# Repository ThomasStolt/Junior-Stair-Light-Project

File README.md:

# Junior-Stair-Light-Project

This is a smaller/easier/cheaper version of my NeoPixel Stair Light Project. The basic idea is to use a bunch of cheap 12V LEDs stripes attached to your indoor stairs, two IR sensors and an Arduino Nano and animate those LED stripes if a person is walking up or down the stairs.

I created this for a friend of mine. He went out on the internet and bought sets of LED stripes (originally thought for cars, 12V) and mounted them under the stairs. I then went ahead and created this little project around it, giving it some more fun.

For several reasons, all grounds of the LED stripes were connected together and all the positive leads were routed to the circuit for switching/PWM. Because of that, I had to use that dual-transistor circuit, which I found on the internet, to be able to switch the positive lines.
It is actually easier to switch the negative lines, that just requires one transistor/MOSFET, so if you do this and you have a choice, you should probably go with that approach.

Nothing more to add really, just read the circuit under schematics/kicad (there is a PDF) and you should be good.

# Needed Materials:

- Power supply, 12V DC, 2A should be enough (I found a 3A in my mess)
- 1 x Arduino Nano
- 2 x 10k resistors (optional, pull up for PIR sensors, I did not need to use them)
- 1 x 5V regulator (L4940V5)
- 2 x 100uF electrolytic capacitor
- 1 x 100nF ceramic capacitor
- a project box to house the electronics

Then _per step_ you need:
- 1 x LED stripe (12V, for cars)
- 2 x 1kOhm resistor
- 1 x 10kOhm resistor
- 1 x BC337 (or similar) NPN Transistor
- 1 x BC327 (or similar) PNP Transistor

Additionally you need a prototype board (or the PCB, see below) for soldering components, some wires for connecting the components, tools (soldering iron, solder, cutter, clippers, a Dremel helps to cut the copper on the board) and some time and patience.

# Printed Circuit Board
I have created a first "Release Candidate" (RC) of a printed circuit board for this project. I added the maximum number of channels (steps) that an Arduino Nano can have, which is number of Digital outputs + number of Analog outputs - 2 analog outputs (for the IR sensors), which should end up at 18.

So, 18 is the maximum number of steps your stairs can have using this single Arduino Nano module. If you have less stairs, just populate the board with the appropriate number of parts for the channels. If you have more stairs - well, you are on your own.

To order the PCB you'll need to send/upload the Gerber files to a PCB manufacturer of your choice. You can find the Gerber files here: [Gerbes](schematics/kicad/GERBERS), just use the ZIP archive. The board is 9cm x 9cm, currently you get special offers for 2$ for 10 pieces - ridicolous!

As of today (Sep 2018), I have not yet ordered a PCB, so I cannot say whether this PCB is really working, it might still be full of bugs! Try at your own risk!

# Steps:
1. buy all the material
2. create the board (see pictures), start with one channel first
3. test that first channel
4. create all the channels
5. stick it to your stairs

# Pictures

This is the finished board, top view.

This is the finished board on a prototype PCB, bottom view.

These are the connectors for the LED strips, power and IR sensors

The test setup for finishing the code.
I did not have enough left over stripes, hence there are some missing here, but that is sufficient.

This can probably be done on one weekend if you are somewhat experienced.

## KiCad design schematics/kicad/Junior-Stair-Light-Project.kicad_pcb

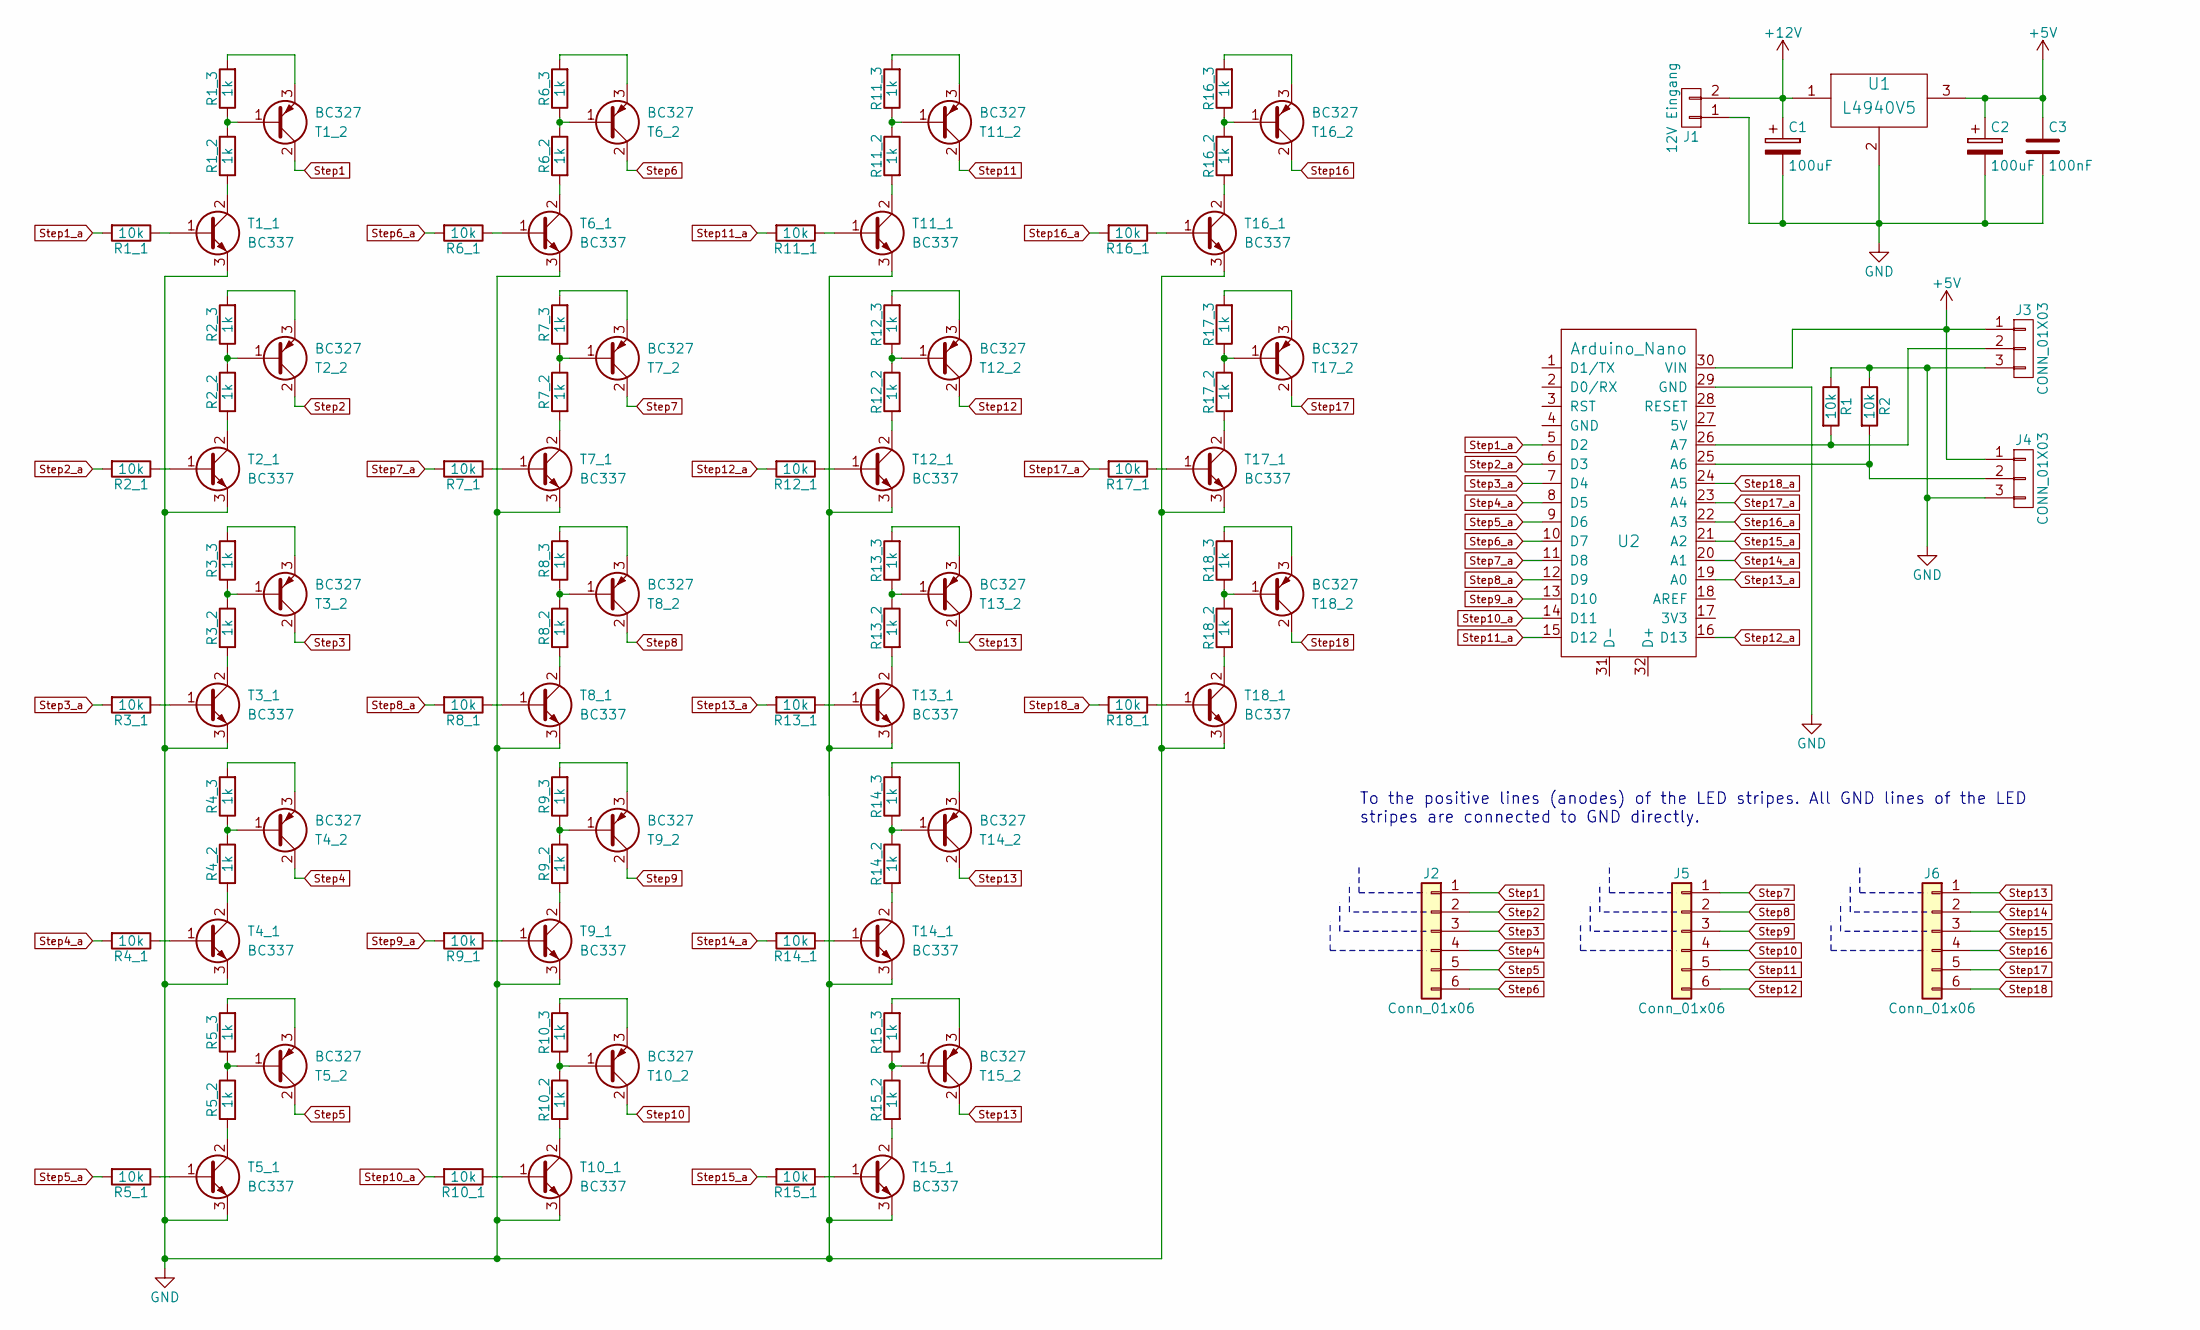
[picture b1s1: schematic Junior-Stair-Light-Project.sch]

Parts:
C1, C2: 100uF; CP_Radial_D7.5mm_P2.50mm
C3: 100nF; C_Disc_D3.8mm_W2.6mm_P2.50mm
J1: 12V Eingang; JST_XH_B02B-XH-A_02x2.50mm_Straight
J2, J5, J6: Conn_01x06; JST_XH_B06B-XH-A_06x2.50mm_Straight
J3, J4: CONN_01X03; JST_XH_B03B-XH-A_03x2.50mm_Straight
R1, R1_1, R2, R2_1, R3_1, R4_1, R5_1, R6_1, R7_1, R8_1, R9_1, R10_1, R11_1, R12_1, R13_1, R14_1, R15_1, R16_1, R17_1, R18_1: 10k; R_Axial_DIN0207_L6.3mm_D2.5mm_P7.62mm_Horizontal
R1_2, R1_3, R2_2, R2_3, R3_2, R3_3, R4_2, R4_3, R5_2, R5_3, R6_2, R6_3, R7_2, R7_3, R8_2, R8_3, R9_2, R9_3, R10_2, R10_3, R11_2, R11_3, R12_2, R12_3, R13_2, R13_3, R14_2, R14_3, R15_2, R15_3, R16_2, R16_3, R17_2, R17_3, R18_2, R18_3: 1k; R_Axial_DIN0207_L6.3mm_D2.5mm_P7.62mm_Horizontal
T1_1, T2_1, T3_1, T4_1, T5_1, T6_1, T7_1, T8_1, T9_1, T10_1, T11_1, T12_1, T13_1, T14_1, T15_1, T16_1, T17_1, T18_1: BC337; TO-92_Inline_Narrow_Oval
T1_2, T2_2, T3_2, T4_2, T5_2, T6_2, T7_2, T8_2, T9_2, T10_2, T11_2, T12_2, T13_2, T14_2, T15_2, T16_2, T17_2, T18_2: BC327; TO-92_Inline_Narrow_Oval
U1: L4940V5; TO-220_Vertical
U2: Arduino_Nano

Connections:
+5V: C2.1, C3.1, J3.1, J4.1, U1.3, U2.30 (VIN)
+12V: C1.1, J1.2, U1.1
GND: C1.2, C2.2, C3.2, J1.1, J3.3, J4.3, R1.1, R2.1, T1_1.3 (E), T2_1.3 (E), T3_1.3 (E), T4_1.3 (E), T5_1.3 (E), T6_1.3 (E), T7_1.3 (E), T8_1.3 (E), T9_1.3 (E), T10_1.3 (E), T11_1.3 (E), T12_1.3 (E), T13_1.3 (E), T14_1.3 (E), T15_1.3 (E), T16_1.3 (E), T17_1.3 (E), T18_1.3 (E), U1.2, U2.29 (GND)
unnamed: J3.2, R1.2, U2.26 (A7)
unnamed: J4.2, R2.2, U2.25 (A6)
unnamed: R1_1.1, T1_1.1 (B)
unnamed: R1_2.1, R1_3.1, T1_2.1 (B)
unnamed: R1_2.2, T1_1.2 (C)
unnamed: R1_3.2, T1_2.3 (E)
unnamed: R2_1.1, T2_1.1 (B)
unnamed: R2_2.1, R2_3.1, T2_2.1 (B)
unnamed: R2_2.2, T2_1.2 (C)
unnamed: R2_3.2, T2_2.3 (E)
unnamed: R3_1.1, T3_1.1 (B)
unnamed: R3_2.1, R3_3.1, T3_2.1 (B)
unnamed: R3_2.2, T3_1.2 (C)
unnamed: R3_3.2, T3_2.3 (E)
unnamed: R4_1.1, T4_1.1 (B)
unnamed: R4_2.1, R4_3.1, T4_2.1 (B)
unnamed: R4_2.2, T4_1.2 (C)
unnamed: R4_3.2, T4_2.3 (E)
unnamed: R5_1.1, T5_1.1 (B)
unnamed: R5_2.1, R5_3.1, T5_2.1 (B)
unnamed: R5_2.2, T5_1.2 (C)
unnamed: R5_3.2, T5_2.3 (E)
unnamed: R6_1.1, T6_1.1 (B)
unnamed: R6_2.1, R6_3.1, T6_2.1 (B)
unnamed: R6_2.2, T6_1.2 (C)
unnamed: R6_3.2, T6_2.3 (E)
unnamed: R7_1.1, T7_1.1 (B)
unnamed: R7_2.1, R7_3.1, T7_2.1 (B)
unnamed: R7_2.2, T7_1.2 (C)
unnamed: R7_3.2, T7_2.3 (E)
unnamed: R8_1.1, T8_1.1 (B)
unnamed: R8_2.1, R8_3.1, T8_2.1 (B)
unnamed: R8_2.2, T8_1.2 (C)
unnamed: R8_3.2, T8_2.3 (E)
unnamed: R9_1.1, T9_1.1 (B)
unnamed: R9_2.1, R9_3.1, T9_2.1 (B)
unnamed: R9_2.2, T9_1.2 (C)
unnamed: R9_3.2, T9_2.3 (E)
unnamed: R10_1.1, T10_1.1 (B)
unnamed: R10_2.1, R10_3.1, T10_2.1 (B)
unnamed: R10_2.2, T10_1.2 (C)
unnamed: R10_3.2, T10_2.3 (E)
unnamed: R11_1.1, T11_1.1 (B)
unnamed: R11_2.1, R11_3.1, T11_2.1 (B)
unnamed: R11_2.2, T11_1.2 (C)
unnamed: R11_3.2, T11_2.3 (E)
unnamed: R12_1.1, T12_1.1 (B)
unnamed: R12_2.1, R12_3.1, T12_2.1 (B)
unnamed: R12_2.2, T12_1.2 (C)
unnamed: R12_3.2, T12_2.3 (E)
unnamed: R13_1.1, T13_1.1 (B)
unnamed: R13_2.1, R13_3.1, T13_2.1 (B)
unnamed: R13_2.2, T13_1.2 (C)
unnamed: R13_3.2, T13_2.3 (E)
unnamed: R14_1.1, T14_1.1 (B)
unnamed: R14_2.1, R14_3.1, T14_2.1 (B)
unnamed: R14_2.2, T14_1.2 (C)
unnamed: R14_3.2, T14_2.3 (E)
unnamed: R15_1.1, T15_1.1 (B)
unnamed: R15_2.1, R15_3.1, T15_2.1 (B)
unnamed: R15_2.2, T15_1.2 (C)
unnamed: R15_3.2, T15_2.3 (E)
unnamed: R16_1.1, T16_1.1 (B)
unnamed: R16_2.1, R16_3.1, T16_2.1 (B)
unnamed: R16_2.2, T16_1.2 (C)
unnamed: R16_3.2, T16_2.3 (E)
unnamed: R17_1.1, T17_1.1 (B)
unnamed: R17_2.1, R17_3.1, T17_2.1 (B)
unnamed: R17_2.2, T17_1.2 (C)
unnamed: R17_3.2, T17_2.3 (E)
unnamed: R18_1.1, T18_1.1 (B)
unnamed: R18_2.1, R18_3.1, T18_2.1 (B)
unnamed: R18_2.2, T18_1.2 (C)
unnamed: R18_3.2, T18_2.3 (E)
Step1: J2.1, T1_2.2 (C)
Step1_a: R1_1.2, U2.5 (D2)
Step2: J2.2, T2_2.2 (C)
Step2_a: R2_1.2, U2.6 (D3)
Step3: J2.3, T3_2.2 (C)
Step3_a: R3_1.2, U2.7 (D4)
Step4: J2.4, T4_2.2 (C)
Step4_a: R4_1.2, U2.8 (D5)
Step5: J2.5, T5_2.2 (C)
Step5_a: R5_1.2, U2.9 (D6)
Step6: J2.6, T6_2.2 (C)
Step6_a: R6_1.2, U2.10 (D7)
Step7: J5.1, T7_2.2 (C)
Step7_a: R7_1.2, U2.11 (D8)
Step8: J5.2, T8_2.2 (C)
Step8_a: R8_1.2, U2.12 (D9)
Step9: J5.3, T9_2.2 (C)
Step9_a: R9_1.2, U2.13 (D10)
Step10: J5.4, T10_2.2 (C)
Step10_a: R10_1.2, U2.14 (D11)
Step11: J5.5, T11_2.2 (C)
Step11_a: R11_1.2, U2.15 (D12)
Step12: J5.6, T12_2.2 (C)
Step12_a: R12_1.2, U2.16 (D13)
Step13: J6.1, T13_2.2 (C), T14_2.2 (C), T15_2.2 (C)
Step13_a: R13_1.2, U2.19 (A0)
Step14: J6.2
Step14_a: R14_1.2, U2.20 (A1)
Step15: J6.3
Step15_a: R15_1.2, U2.21 (A2)
Step16: J6.4, T16_2.2 (C)
Step16_a: R16_1.2, U2.22 (A3)
Step17: J6.5, T17_2.2 (C)
Step17_a: R17_1.2, U2.23 (A4)
Step18: J6.6, T18_2.2 (C)
Step18_a: R18_1.2, U2.24 (A5)

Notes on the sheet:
To the positive lines (anodes) of the LED stripes. All GND lines of the LED stripes are connected to GND directly.

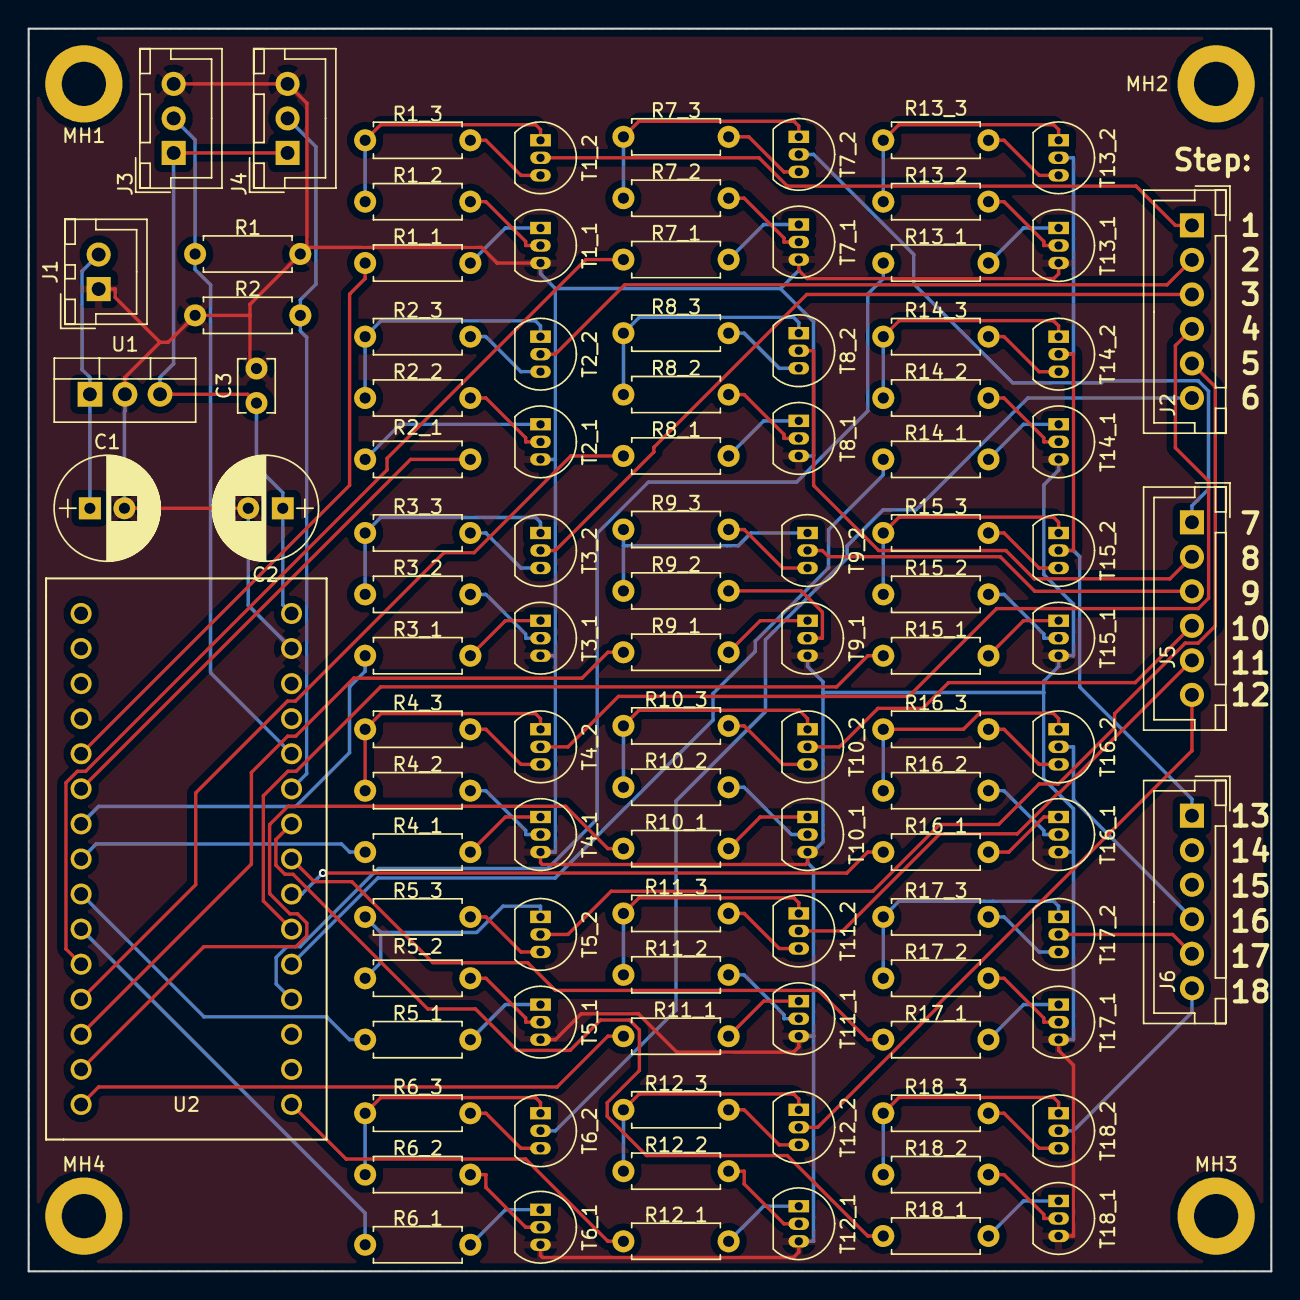
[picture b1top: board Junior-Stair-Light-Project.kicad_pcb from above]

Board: 2 copper layers, 90.0 x 90.0 mm, 107 parts (0 on the bottom side), 111 nets.

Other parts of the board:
MH1: MH1; MountingHole_3.2mm_M3_DIN965_Pad
MH2: MH2; MountingHole_3.2mm_M3_DIN965_Pad
MH3: MH3; MountingHole_3.2mm_M3_DIN965_Pad
MH4: MH4; MountingHole_3.2mm_M3_DIN965_Pad

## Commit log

2018-04-16 changed 12v switching
2018-04-16 First edition of PCB done
2018-04-16 started Wiki
2018-04-29 new stuff
2018-08-31 Some changes
2018-08-31 First RC of code is ready
2018-08-31 Some code cleanup
2018-08-31 Update README.md with basics
2018-08-31 Cleanup
2018-08-31 added picture
2018-09-03 Added max channels (19) and finished first RC of PCB layout
2018-09-03 Created gerber files
2018-09-03 Corrected connectivity, there was a bug
2018-09-03 Updates, updates, updates
2018-09-03 some cleanup
